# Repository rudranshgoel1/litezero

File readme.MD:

# litezero

### Why did I make it?
bcz i need more hardware projects in my portfolio and also because it seemed like a fun hardware project which was kinda beginner friendly. ALSO I NEEDED A FLIPPER ZERO BUT IT IS SO EXPENSIVE AHHH

### What was the hardest part about this ?
honestly speaking, routing.

Features:

- 2x NRF24L01 for 2.4ghz wireless stuff
- 1x CC1101 for 433 mhz wireless stuff
- 2 status LEDs
- 2 IR LEDs (universal remote)
- 3x tactile buttons to control
- 1x 0.96 inch display for seeing what is going on
- 1x inmp441 for voice commands
- 1x sd card reader to store data
- 1x PN532 breakout board for NFC
- ESP32 S3 WROOM1-N16R8 as the main brain

### How to build it?
1. Order the PCB (with PCBA) from JLCPCB or any PCB manufacturer.
2. Order the different parts from the vendors (available)
3. Solder the NRF modules, LEDs, buttons, SD Card reader and the display on the front side
4. Solder the PN532 board on the back side
5. Use the code given in /prod/firmware and upload it by connecting through the USB C port to your computer and using the Arduino IDE.
6. Give it power through the USB port, then navigate through the buttons and the display attached.
7. voila! now you have a custom built flipper zero!

**DISCLAIMER:** This tool is intended for educational and research purposes only. I do not condone or endorse any illegal, malicious, or unauthorized use of this tool. Misuse includes, but is not limited to, unauthorized access to systems or networks, data theft, spreading malware, compromising accounts, violating others' privacy, disrupting services, or running code with the intent to cause harm. Users are solely responsible for how they use this tool and any code they execute with it. Always obtain proper authorization before testing systems or running security-related experiments.

### Schematic

### PCB 

### 3D view of all parts 

## BOM

[BOM](BOM.csv)
|Name                               |Purpose                 |Quantity|Total Cost (USD)|Link                                                                                                                   |Distributor |
|-----------------------------------|------------------------|--------|----------------|-----------------------------------------------------------------------------------------------------------------------|------------|
|ESP32-S3 WROOM 1                   |Main MCU                |1       |4.69            |https://robu.in/product/espressif-esp32-s3-wroom-1-n16r8-module/                                                       |Robu        |
|NRF24L01 PA+LNA                    |2.4ghz wireless antenna |2       |3.54            |https://robu.in/product/2-4ghz-nrf24l01palna-sma-antenna-wireless-transceiver-communication-module-1km/                |Robu        |
|CC1101                             |433 mhz wireless antenna|1       |3.54            |https://quartzcomponents.com/products/cc1101-sma-antenna-wireless-transceiver-module                                   |Quartz      |
|SD Card Reader                     |For storage purpose     |1       |0.44            |https://www.flyrobo.in/micro-sd-card-reader-module-for-arduino                                                         |Fly Robo    |
|0.96 inch display                  |Display                 |1       |1.5             |https://quartzcomponents.com/collections/all/products/oled-display-0-96-inch-i2c-interface-4-pin-blue-ssd1306          |Quartz      |
|INMP441                            |Microphone              |1       |1.52            |https://quartzcomponents.com/collections/all/products/inmp441-mems-high-precision-omnidirectional-microphone-module-i2s|Quartz      |
|6mm Tactile Buttons                |Buttons for navigation  |3       |0.1             |https://quartzcomponents.com/collections/all/products/6-6-4-3mm-pcb-momentary-tactile-push-button-switch               |Quartz      |
|Status and Power LED               |Status and Power LED    |2       |0               |SELF SOURCED                                                                                                           |SELF SOURCED|
|IR LED                             |IR LED                  |2       |0.1             |https://quartzcomponents.com/collections/all/products/l518eir1bc1-s61-940nm-5mm-infrared-ir-transmitter-led            |Quartz      |
|2N3904                             |Controlling IR          |1       |0.04            |https://quartzcomponents.com/collections/all/products/2n3904-npn-general-purpose-transistor                            |Quartz      |
|TSOP38238 IR Receiver Diode (38kHz)|Controlling IR          |1       |0.14            |https://quartzcomponents.com/collections/all/products/tsop38238-ir-receiver-diode-38khz                                |Quartz      |
|PN532                              |NFC                     |1       |2.77            |https://quartzcomponents.com/products/pn532-rfid-reader-nfc-read-write-module                                          |Quartz      |
|PCB + PCBA                         |Main PCBs + PCBA        |5       |27.82           |https://jlcpcb.com/                                                                                                    |JLPCB       |
|                                   |                        |        |                |                                                                                                                       |            |
|                                   |                        |        |46.2            |                                                                                                                       |            |

## Total Pricing

Final Price comes out to be 4,410 INR ($46.2) [ SHIPPING INCLUDED ]

The pricing might slightly vary due to flash sales, and dollar market trends.

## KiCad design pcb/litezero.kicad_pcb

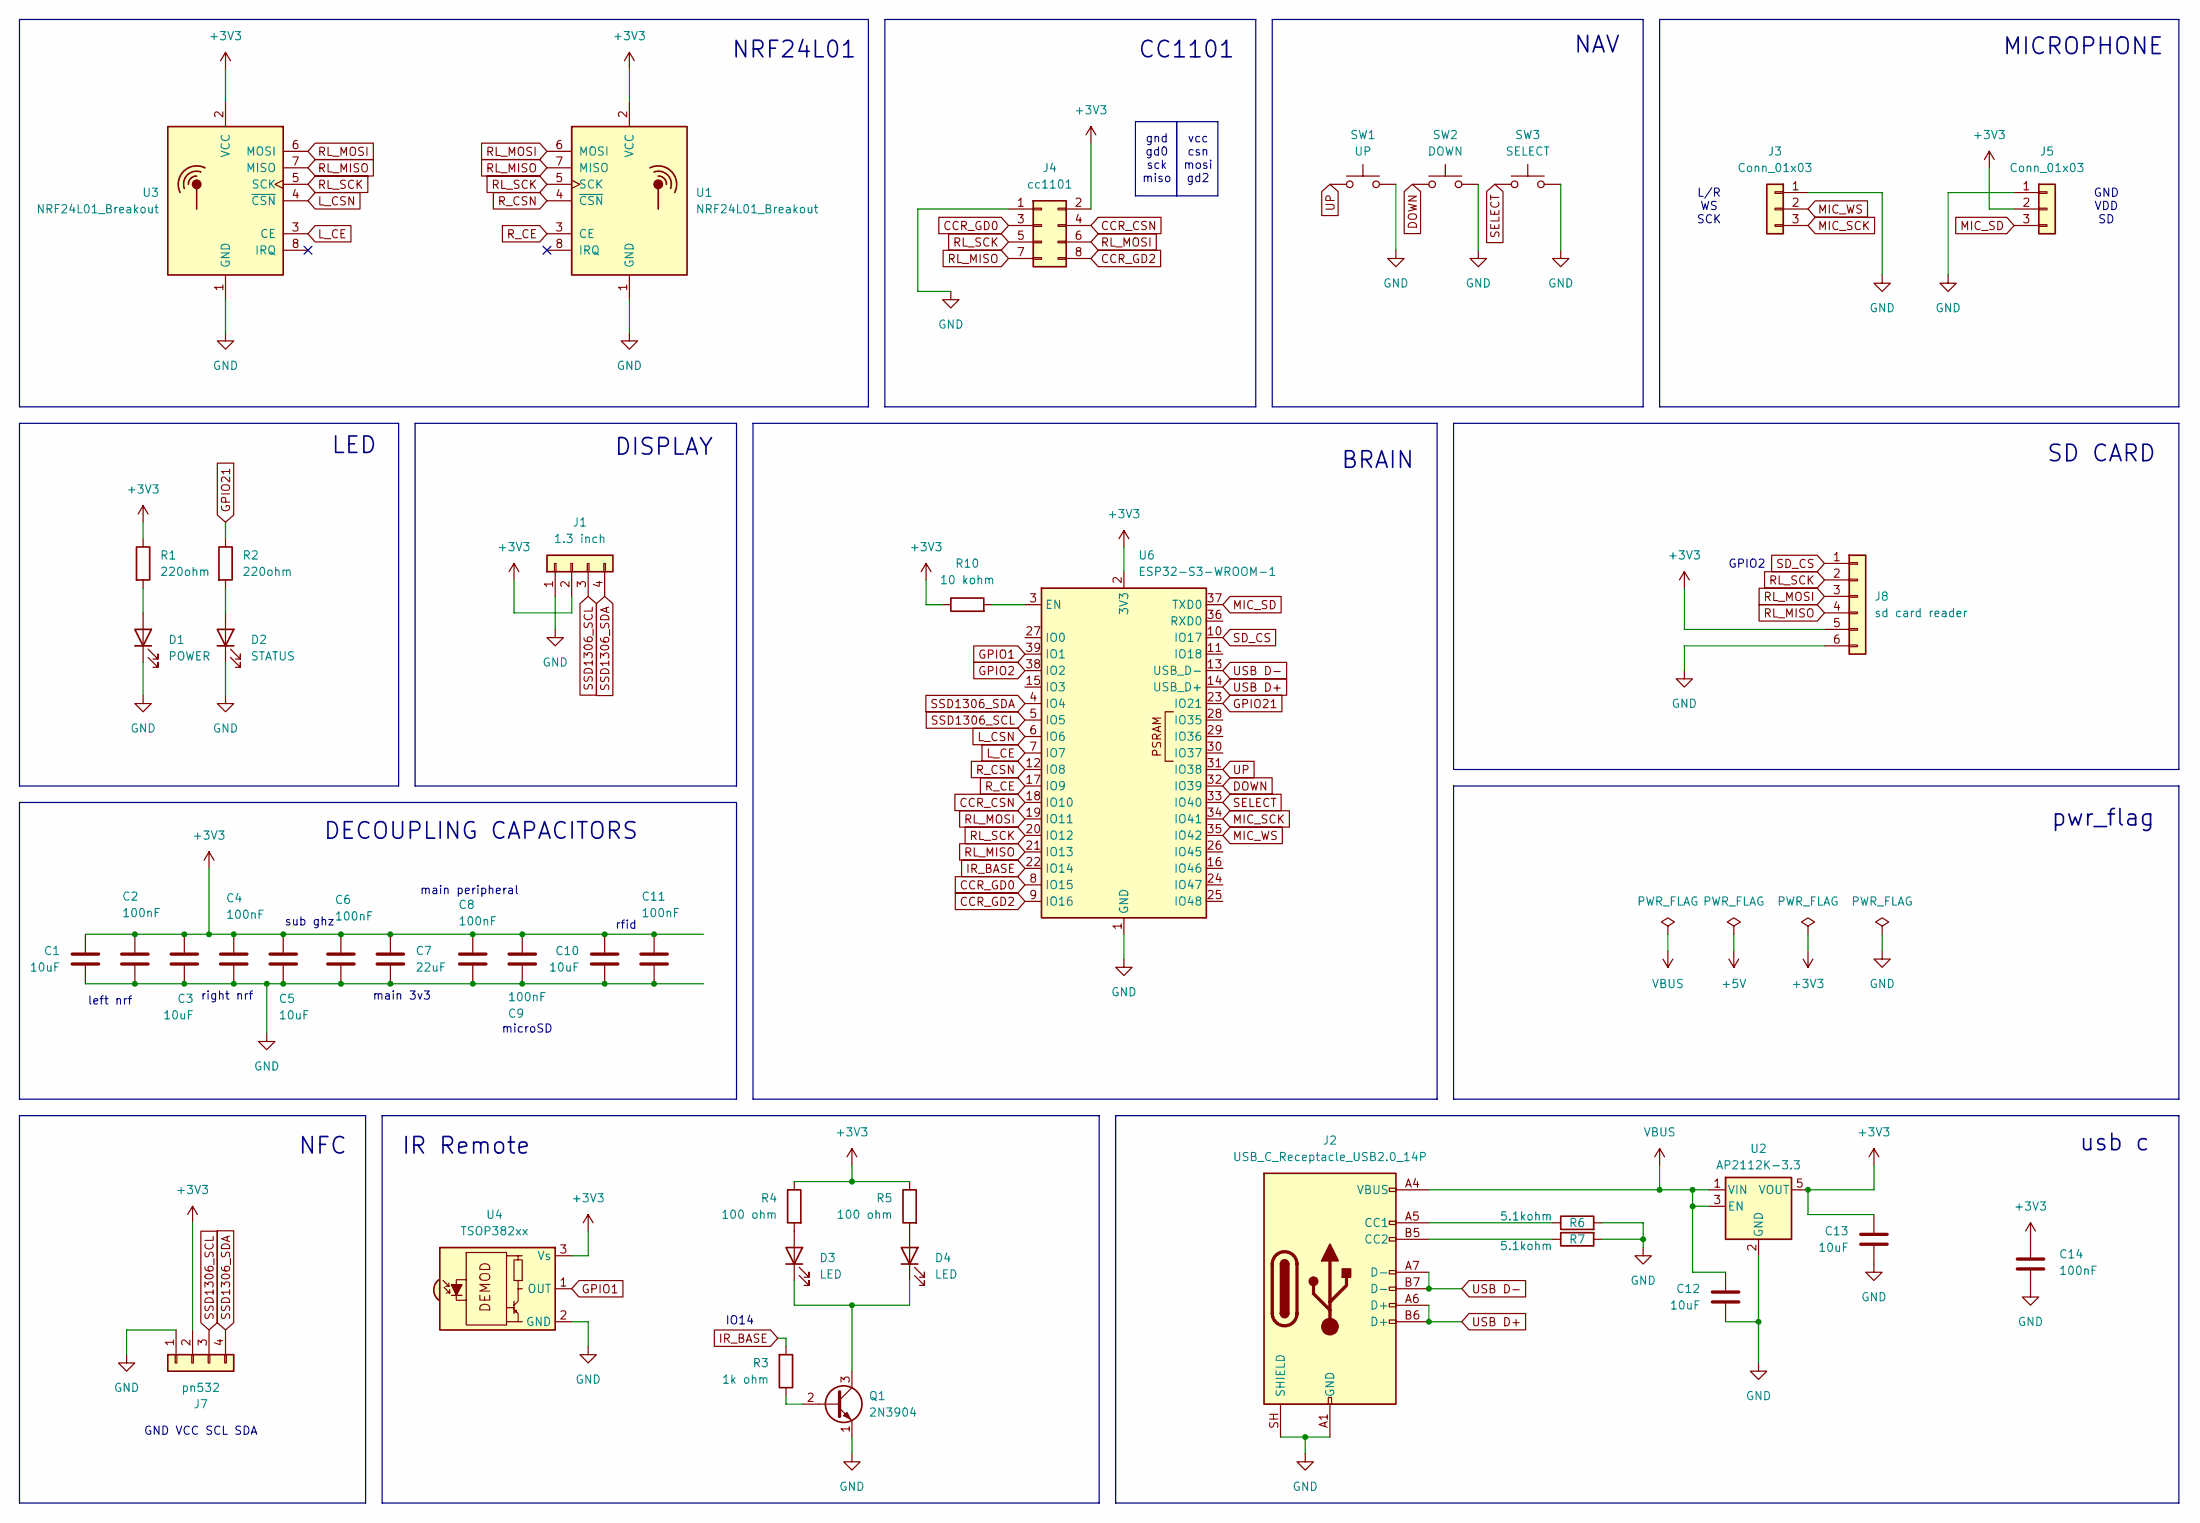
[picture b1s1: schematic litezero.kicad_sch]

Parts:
C1, C3, C5, C10, C12, C13: 10uF; C_0805_2012Metric_Pad1.18x1.45mm_HandSolder
C2, C4, C6, C8, C9, C11, C14: 100nF; C_0805_2012Metric_Pad1.18x1.45mm_HandSolder
C7: 22uF; C_0805_2012Metric_Pad1.18x1.45mm_HandSolder
D1: POWER; LED_D5.0mm
D2: STATUS; LED_D5.0mm
D3, D4: LED; LED_D5.0mm
J1: 1.3 inch; PinHeader_1x04_P2.54mm_Vertical
J2: USB_C_Receptacle_USB2.0_14P; USB_C_Receptacle_HRO_TYPE-C-31-M-12
J3, J5: Conn_01x03; PinHeader_1x03_P2.54mm_Vertical
J4: cc1101; PinHeader_2x04_P2.54mm_Vertical
J7: pn532; PinHeader_1x04_P2.54mm_Vertical
J8: sd card reader; PinHeader_1x06_P2.54mm_Vertical
Q1: 2N3904; TO-92_Inline
R1, R2: 220ohm; R_0805_2012Metric_Pad1.20x1.40mm_HandSolder
R3: 1k ohm; R_0805_2012Metric_Pad1.20x1.40mm_HandSolder
R4, R5: 100 ohm; R_0805_2012Metric_Pad1.20x1.40mm_HandSolder
R6, R7: 5.1kohm; R_0805_2012Metric_Pad1.20x1.40mm_HandSolder
R10: 10 kohm; R_0805_2012Metric_Pad1.20x1.40mm_HandSolder
SW1: UP; SW_PUSH_6mm
SW2: DOWN; SW_PUSH_6mm
SW3: SELECT; SW_PUSH_6mm
U1, U3: NRF24L01_Breakout; nRF24L01_Breakout
U2: AP2112K-3.3; SOT-23-5
U4: TSOP382xx; Vishay_MINICAST-3Pin
U6: ESP32-S3-WROOM-1

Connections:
+3V3: C1.1, C2.1, C3.1, C4.1, C5.1, C6.1, C7.1, C8.1, C9.2, C10.1, C11.1, C13.1, C14.1, J1.2, J4.2, J5.2, J7.2, J8.5, R1.1, R4.1, R5.1, R10.1, U1.2 (VCC), U2.5 (VOUT), U3.2 (VCC), U4.3 (Vs), U6.2 (3V3)
CCR_CSN: J4.4, U6.18 (IO10)
CCR_GD0: J4.3, U6.8 (IO15)
CCR_GD2: J4.8, U6.9 (IO16)
DOWN: SW2.1, U6.32 (IO39)
GND: C1.2, C2.2, C3.2, C4.2, C5.2, C6.2, C7.2, C8.2, C9.1, C10.2, C11.2, C12.2, C13.2, C14.2, D1.1 (K), D2.1 (K), J1.1, J2.A1 (GND), J2.A12 (GND), J2.B1 (GND), J2.B12 (GND), J2.SH (SHIELD), J3.1, J4.1, J5.1, J7.1, J8.6, Q1.1 (E), R6.2, R7.2, SW1.2, SW2.2, SW3.2, U1.1 (GND), U2.2 (GND), U3.1 (GND), U4.2 (GND), U6.1 (GND), U6.40 (GND), U6.41 (GND)
GPIO1: U4.1 (OUT), U6.39 (IO1)
GPIO2: U6.38 (IO2)
GPIO21: R2.1, U6.23 (IO21)
IR_BASE: R3.2, U6.22 (IO14)
L_CE: U3.3 (CE), U6.7 (IO7)
L_CSN: U3.4 (~CSN), U6.6 (IO6)
MIC_SCK: J3.3, U6.34 (IO41)
MIC_SD: J5.3, U6.37 (TXD0)
MIC_WS: J3.2, U6.35 (IO42)
unnamed: D1.2 (A), R1.2
unnamed: D2.2 (A), R2.2
unnamed: D3.2 (A), R4.2
unnamed: D3.1 (K), D4.1 (K), Q1.3 (C)
unnamed: D4.2 (A), R5.2
unnamed: J2.A5 (CC1), R6.1
unnamed: J2.B5 (CC2), R7.1
unnamed: Q1.2 (B), R3.1
unnamed: R10.2, U6.3 (EN)
RL_MISO: J4.7, J8.4, U1.7 (MISO), U3.7 (MISO), U6.21 (IO13)
RL_MOSI: J4.6, J8.3, U1.6 (MOSI), U3.6 (MOSI), U6.19 (IO11)
RL_SCK: J4.5, J8.2, U1.5 (SCK), U3.5 (SCK), U6.20 (IO12)
R_CE: U1.3 (CE), U6.17 (IO9)
R_CSN: U1.4 (~CSN), U6.12 (IO8)
SD_CS: J8.1, U6.10 (IO17)
SELECT: SW3.1, U6.33 (IO40)
SSD1306_SCL: J1.3, J7.3, U6.5 (IO5)
SSD1306_SDA: J1.4, J7.4, U6.4 (IO4)
UP: SW1.1, U6.31 (IO38)
USB D+: J2.A6 (D+), J2.B6 (D+), U6.14 (USB_D+)
USB D-: J2.A7 (D-), J2.B7 (D-), U6.13 (USB_D-)
VBUS: C12.1, J2.A4 (VBUS), J2.A9 (VBUS), J2.B4 (VBUS), J2.B9 (VBUS), U2.1 (VIN), U2.3 (EN)

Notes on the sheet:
gnd gd0 sck miso
rfid
DECOUPLING CAPACITORS
NAV
MICROPHONE
sub ghz
CC1101
NRF24L01
right nrf
LED
IR Remote
NFC
GPIO2
DISPLAY
vcc csn mosi gd2
main peripheral
BRAIN
main 3v3
pwr_flag
GND VCC SCL SDA
GND VDD SD
L/R WS SCK
left nrf
usb c
IO14
microSD
SD CARD

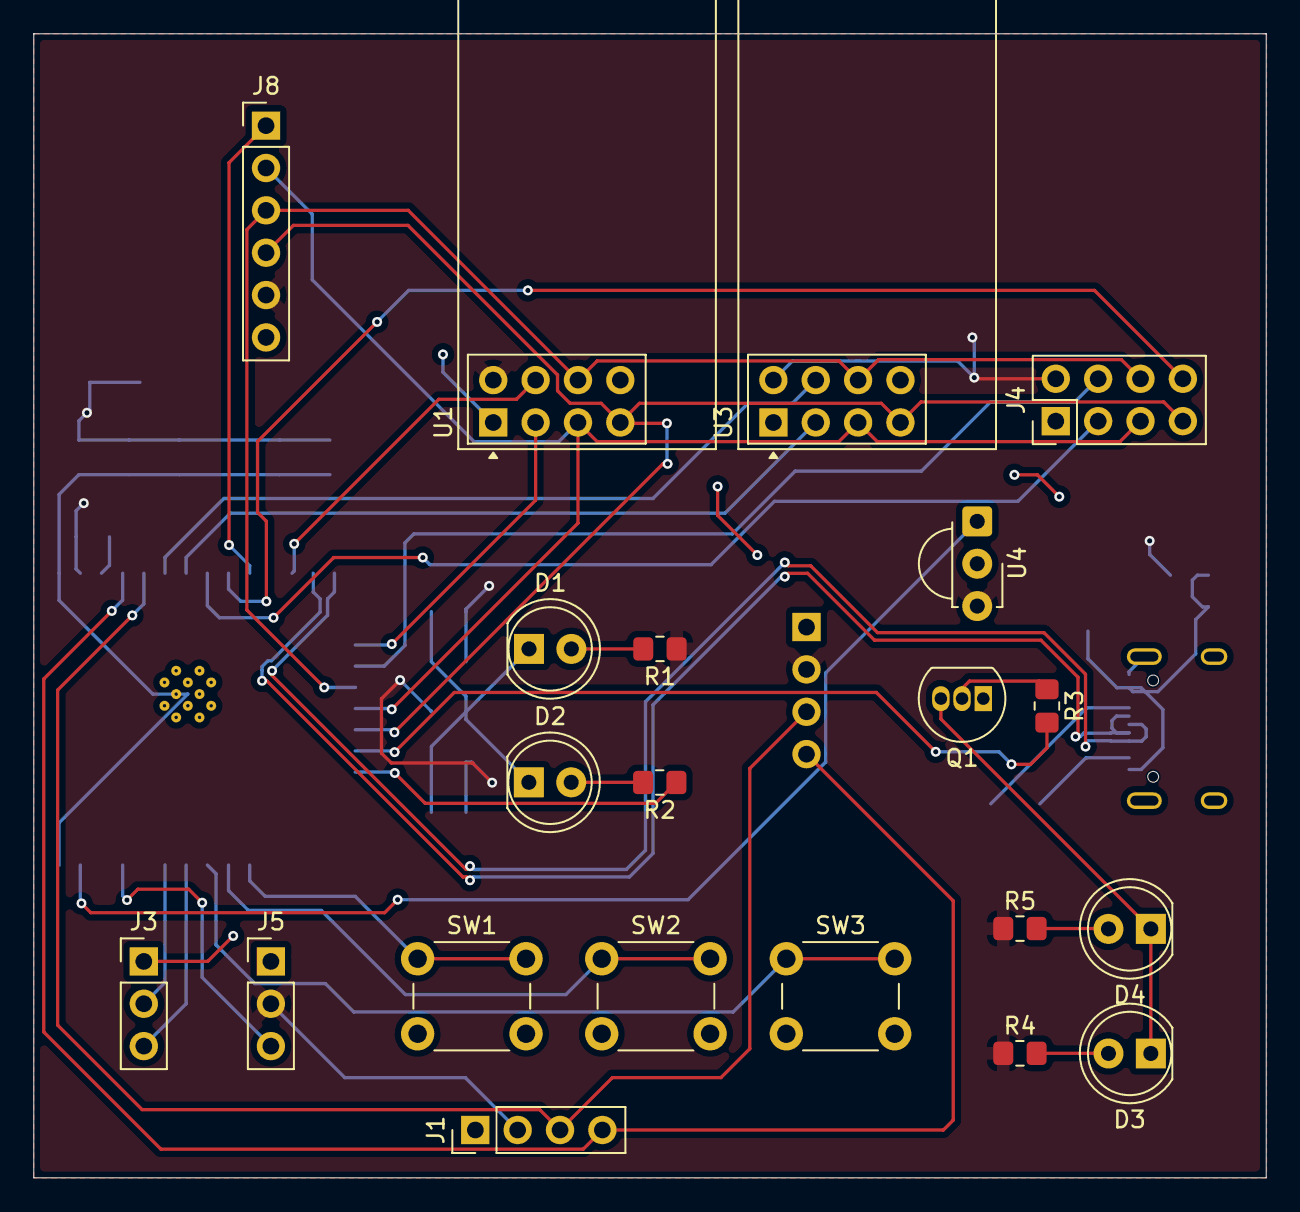
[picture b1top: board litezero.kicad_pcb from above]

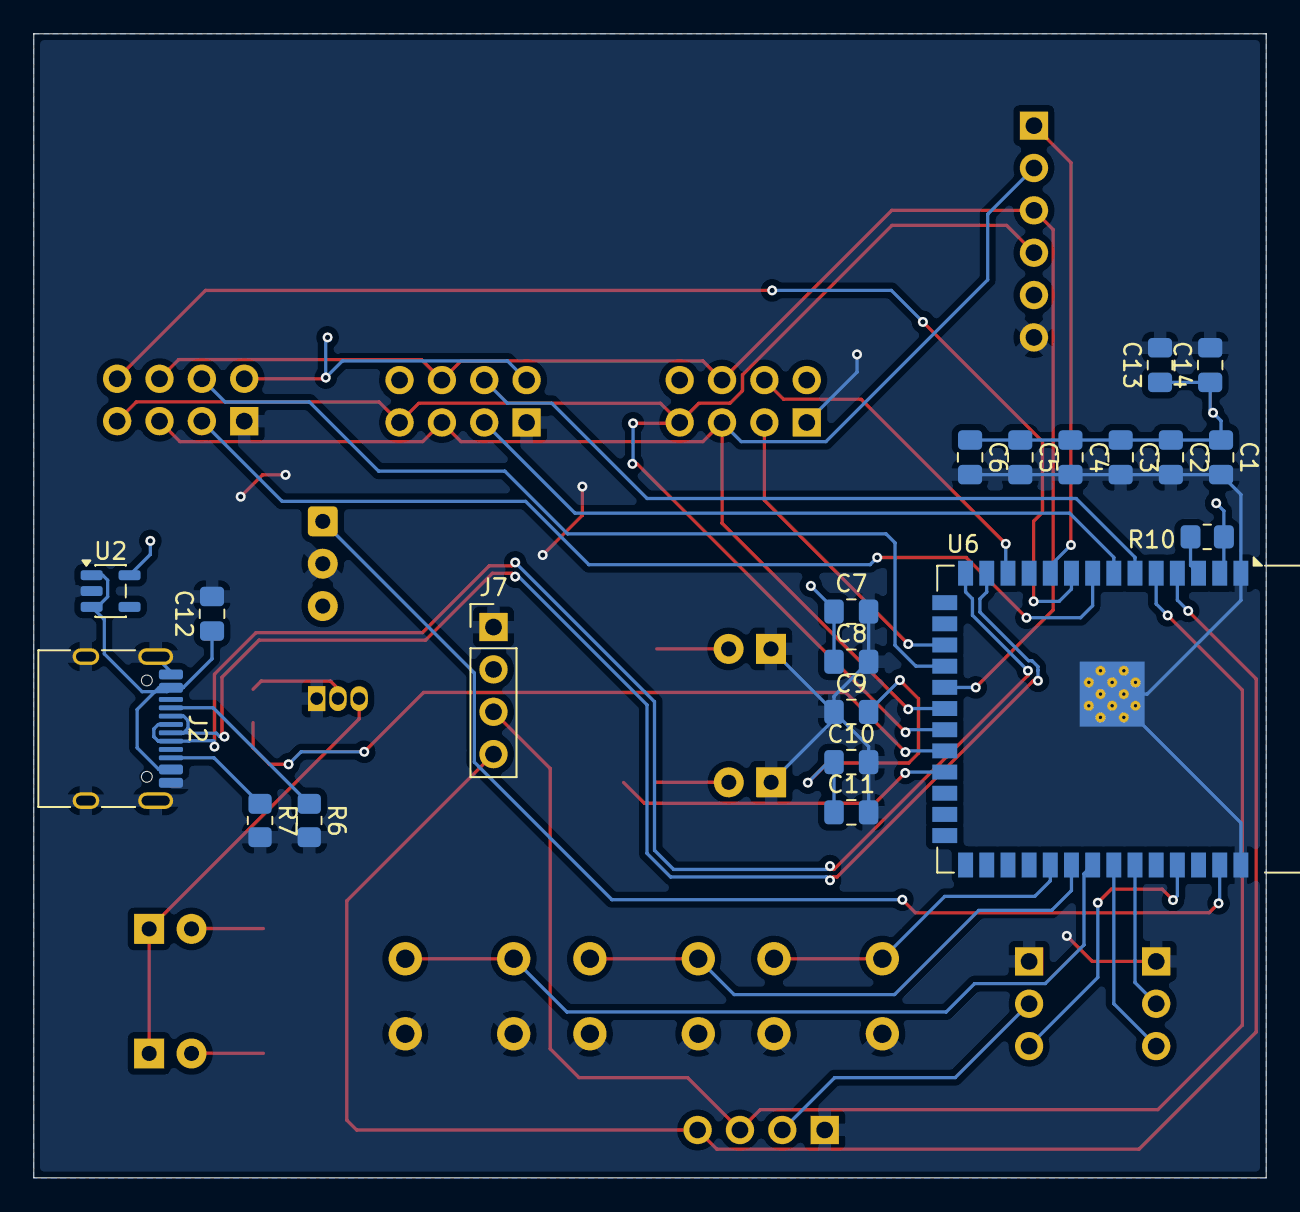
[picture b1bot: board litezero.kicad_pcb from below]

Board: 2 copper layers, 73.9 x 68.6 mm, 42 parts (21 on the bottom side), 36 nets.
